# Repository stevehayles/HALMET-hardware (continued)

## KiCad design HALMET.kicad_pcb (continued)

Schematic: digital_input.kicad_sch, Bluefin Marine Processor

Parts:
C1101, C1102, C1103, C1112: 3.3nF; C_0402_1005Metric; LCSC C26404
C1104, C1105, C1106, C1107: 220pF; R_0402_1005Metric; LCSC C1530
C1113, C1114, C1115, C1116: 100nF; C_0402_1005Metric; LCSC C1525
D1103, D1104, D1105, D1113: BAT54S; SOT-323_SC-70; LCSC C12741
J1103, J1104, J1105, J1106: Conn_01x02; PhoenixContact_MCV_1,5_2-G-3.81_1x02_P3.81mm_Vertical; LCSC C8396
JP1101, JP1102, JP1103, JP1104, JP1105, JP1106, JP1107, JP1108, JP1109, JP1110, JP1111, JP1112: SolderJumper_2_Open; SolderJumper-2_P1.3mm_Open_TrianglePad_Narrow
R1101, R1102, R1104, R1105: 20k; R_0603_1608Metric; LCSC C4184
R1106, R1107, R1108, R1109: 100k; R_0402_1005Metric; LCSC C25741
U1101, U1102, U1103, U1104: 74LVC1G17; SOT-353_SC-70-5; LCSC C212314

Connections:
+3.3V_1: C1113.1, C1114.1, C1115.1, C1116.1, D1103.2 (K), D1104.2 (K), D1105.2 (K), D1113.2 (K), JP1106.2 (B), JP1107.2 (B), JP1109.2 (B), JP1111.2 (B), U1101.5 (VCC), U1102.5 (VCC), U1103.5 (VCC), U1104.5 (VCC); also elsewhere on the board
/Digital input/DigIn1: U1101.4; also elsewhere on the board
/Digital input/DigIn2: U1102.4; also elsewhere on the board
/Digital input/DigIn3: U1103.4; also elsewhere on the board
/Digital input/DigIn4: U1104.4; also elsewhere on the board
/Digital input/In1: J1103.2, R1101.2
/Digital input/In2: J1104.2, R1102.2
/Digital input/In3: J1105.2, R1104.2
/Digital input/In4: J1106.2, R1105.2
/Digital input/Inp1: C1104.1, D1113.3 (COM), JP1101.1 (A), R1101.1, R1106.2, U1101.2
/Digital input/Inp2: C1105.1, D1103.3 (COM), JP1102.1 (A), R1102.1, R1107.2, U1102.2
/Digital input/Inp3: C1106.1, D1104.3 (COM), JP1103.1 (A), R1104.1, R1108.2, U1103.2
/Digital input/Inp4: C1107.1, D1105.3 (COM), JP1104.1 (A), R1105.1, R1109.2, U1104.2
GND1: C1101.2, C1102.2, C1103.2, C1104.2, C1105.2, C1106.2, C1107.2, C1112.2, C1113.2, C1114.2, C1115.2, C1116.2, D1103.1 (A), D1104.1 (A), D1105.1 (A), D1113.1 (A), J1103.1, J1104.1, J1105.1, J1106.1, JP1105.1 (A), JP1108.1 (A), JP1110.1 (A), JP1112.1 (A), U1101.3 (GND), U1102.3 (GND), U1103.3 (GND), U1104.3 (GND); also elsewhere on the board
unnamed: C1112.1, JP1101.2 (B)
unnamed: C1101.1, JP1102.2 (B)
unnamed: C1102.1, JP1103.2 (B)
unnamed: C1103.1, JP1104.2 (B)
unnamed: JP1105.2 (B), JP1106.1 (A), R1106.1
unnamed: JP1107.1 (A), JP1108.2 (B), R1107.1
unnamed: JP1109.1 (A), JP1110.2 (B), R1108.1
unnamed: JP1111.1 (A), JP1112.2 (B), R1109.1

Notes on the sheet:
RC LP filter with fc = 36 kHz
Clamp input to rails
Input Connectors
Optional pull-up or pull-down for different NO/NC switch configurations.
Solder jumpers enable optional lowpass filters with f_c at 2.3 kHz
Limit input current in clamped operation

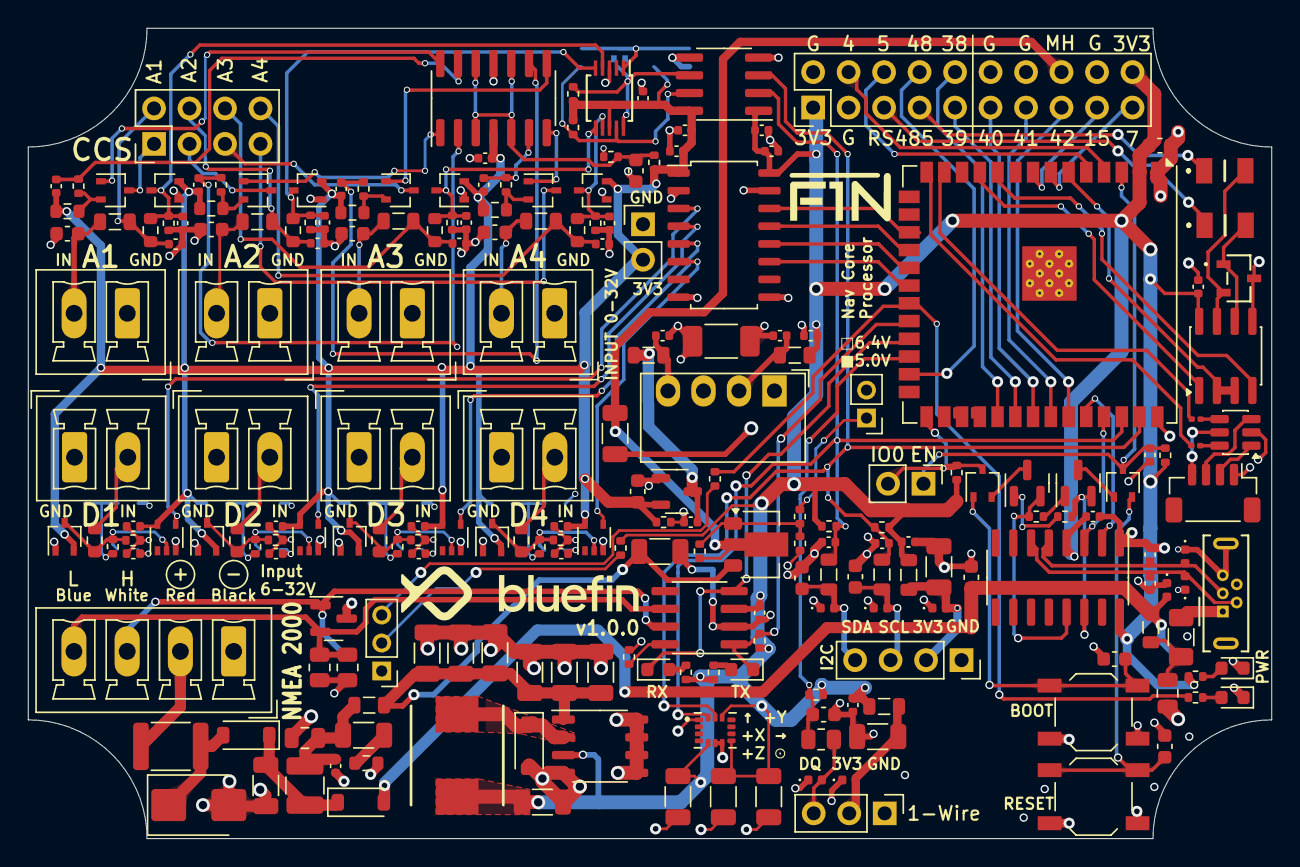
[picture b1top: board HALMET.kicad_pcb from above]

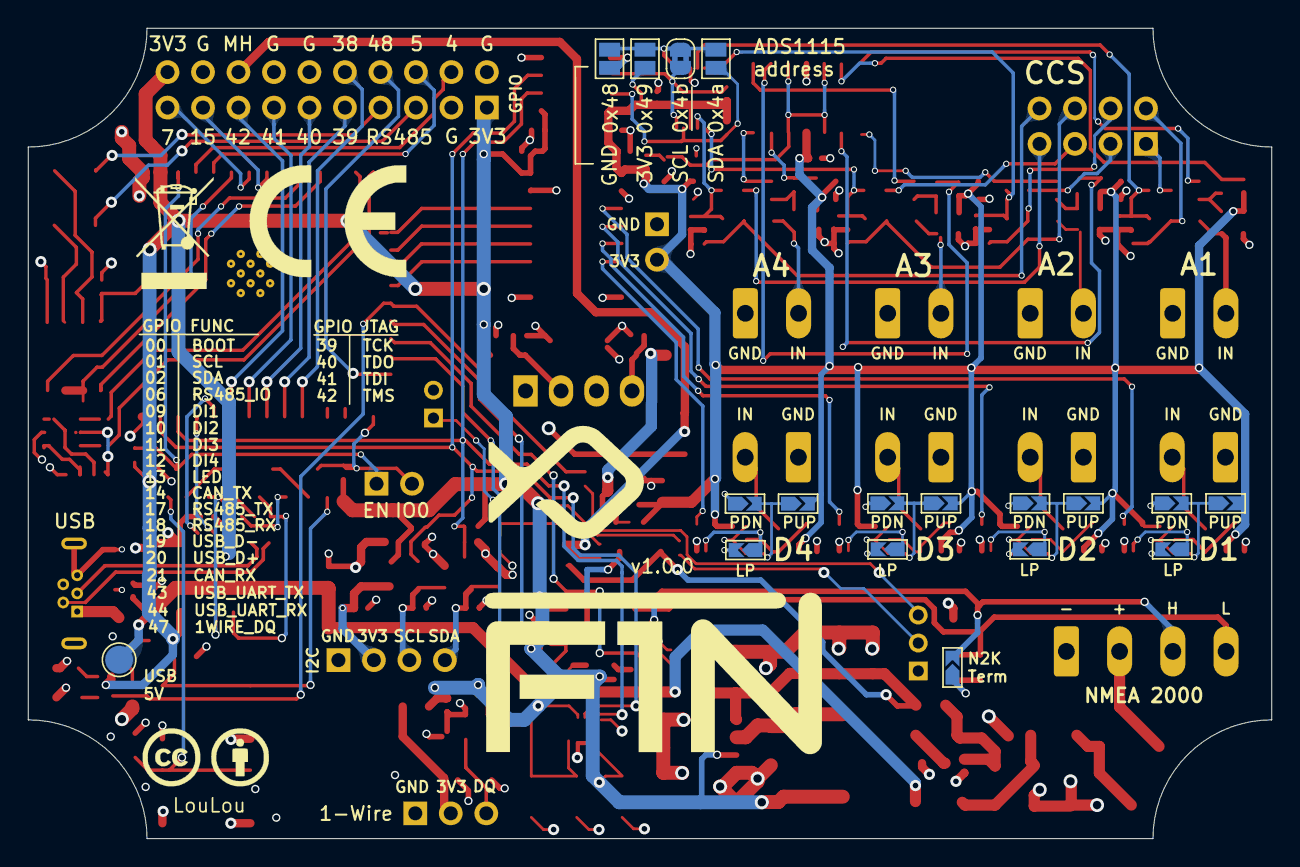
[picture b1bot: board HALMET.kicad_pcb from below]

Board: 4 copper layers, 89.0 x 58.0 mm, 243 parts (20 on the bottom side), 135 nets.

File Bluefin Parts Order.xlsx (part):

Reference | Qty | Value | DNP | Exclude from BOM | Exclude from Board | Footprint | Datasheet | LCSC | JLCPCB_CORRECTION |  |  | New
C1101,C1102,C1103,C1112 | 4 | 3.3nF |  |  |  | Capacitor_SMD:C_0402_1005Metric | ~ | C26404 |  |  |  | 0
C1104,C1105,C1106,C1107 | 4 | 220pF |  |  |  | Resistor_SMD:R_0402_1005Metric | ~ | C1530 |  |  |  | 0
C1201,C1202,C1208,C1210 | 4 | 4.7uF |  |  |  | Capacitor_SMD:C_0402_1005Metric | ~ | C23733 |  |  |  | 0
C1203 | 1 | 10uF/10V |  |  |  | Capacitor_SMD:C_0603_1608Metric | ~ | C19702 |  |  |  | 0
C1209 | 1 | 220pF/2kV |  |  |  | HALMET:C_1808_4520Metric | ~ | C2940747 |  |  |  | 0
C202 | 1 | 22uF |  |  |  | Capacitor_SMD:C_0603_1608Metric | ~ | C59461 |  |  |  | 0
C203 | 1 | 1uF |  |  |  | Capacitor_SMD:C_0402_1005Metric | ~ | C52923 |  |  |  | 0
C304 | 1 | 47uF/6.3V |  |  |  | Capacitor_SMD:C_1206_3216Metric | ~ | C96123 |  |  |  | 0
C402 | 1 | 4.7uF/16V |  |  |  | Capacitor_SMD:C_0603_1608Metric | ~ | C19666 |  |  |  | 0
C403,C404 | 2 | 10pF/50V |  | Excluded from BOM |  | Capacitor_SMD:C_0402_1005Metric | ~ | C32949 |  |  |  | 0
C501,C502 | 2 | 100nF/50V |  |  |  | Capacitor_SMD:C_0603_1608Metric | ~ | C14663 |  |  |  | 0
C503,C715 | 2 | 1uF/50V |  |  |  | Capacitor_SMD:C_0805_2012Metric | ~ | C28323 |  |  |  | 0
C601,C604,C612,C614,C705,C706 | 6 | 33pF/50V |  |  |  | Capacitor_SMD:C_0603_1608Metric | ~ | C1663 |  |  |  | 0
C602,C606,C607,C608,C609,C610,C616,C624,C901,C1113,C1114,C1115,C1116,C1204,C120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 | 17 | 100nF |  |  |  | Capacitor_SMD:C_0402_1005Metric | ~ | C1525 |  |  |  | 1
C603,C605,C613,C615,C702,C703 | 6 | 33pF |  |  |  | Capacitor_SMD:C_0402_1005Metric | ~ | C1562 |  |  |  | 0
C611 | 1 | 68nF |  |  |  | Capacitor_SMD:C_0603_1608Metric | ~ | C31658 |  |  |  | 0
C620,C621,C622,C623 | 4 | 10nF |  |  |  | Capacitor_SMD:C_0402_1005Metric | ~ | C15195 |  |  |  | 0
C701,C801 | 2 | 10uF |  |  |  | Capacitor_SMD:C_0402_1005Metric | ~ | C15525 |  |  |  | 0
C704,C707,C708,C709,C710,C711,C712,C714,C721,C803 | 10 | 10uF/50V |  |  |  | Capacitor_SMD:C_1206_3216Metric | ~ | C13585 |  |  |  | 1
C713 | 1 | 4.7nF/50V |  |  |  | Capacitor_SMD:C_0402_1005Metric | ~ | C1538 |  |  |  | 0
C716 | 1 | 4.7uF/50V |  |  |  | Capacitor_SMD:C_1206_3216Metric | ~ | C29823 |  |  |  | 0
C717,C720 | 2 | 0.1uF/50V |  |  |  | Capacitor_SMD:C_1206_3216Metric | ~ | C24497 |  |  |  | 1
C718 | 1 | 2.2uF/50V |  |  |  | Capacitor_SMD:C_1206_3216Metric | ~ | C50254 |  |  |  | 1
C719 | 1 | 10nF/50V |  |  |  | Capacitor_SMD:C_1206_3216Metric | ~ | C153292 |  |  |  | 1
C802 | 1 | 1nF/50V |  |  |  | Capacitor_SMD:C_0603_1608Metric | ~ | C1588 |  |  |  | 0
CR501 | 1 | PSM712-LF-T7 |  |  |  | PSM712-LF-T7:CR_SOT-23_PTD | PSM712-LF-T7 | C32677 |  |  |  | 1
D1001,D1002 | 2 | GREEN LED |  |  |  | LED_SMD:LED_0603_1608Metric | ~ | C965804 |  |  |  | 0
D1101,D1102 | 2 | BAT54A |  |  |  | Package_TO_SOT_SMD:SOT-323_SC-70 |  | C78261 | 0;0;180 |  |  | 0
D201,D303,D701 | 3 | B5819W |  |  |  | Diode_SMD:D_SOD-123 | ~ | C8598 |  |  |  | 0
D301 | 1 | SMBJ33CA |  |  |  | Diode_SMD:D_SMB | ~ | C114000 |  |  |  | 0
D401,D402,D403,D503,D504,D903,D904,D905 | 8 | ESD5451N |  |  |  | Diode_SMD:D_0402_1005Metric | ~ | C2936977 |  |  |  | 0
D501 | 1 | BLUE LED |  |  |  | LED_SMD:LED_0603_1608Metric | ~ | C84266 |  |  |  | 0
D502 | 1 | RED LED |  |  |  | LED_SMD:LED_0603_1608Metric | ~ | C2286 |  |  |  | 0
D603,D604,D605,D611,D1103,D1104,D1105,D1113 | 8 | BAT54S |  |  |  | Package_TO_SOT_SMD:SOT-323_SC-70 | https://www.diodes.com/assets/Datasheets/ds11005.pdf | C12741 | 0;0;180 |  |  | 0
D801 | 1 | SM24CANB |  |  |  | Package_TO_SOT_SMD:SOT-23 | ~ | C41376477 | 0;0;180 |  |  | 0
F301 | 1 | mSMD050-60V |  |  |  | Fuse:Fuse_1812_4532Metric | ~ | C70113 |  |  |  | 0
F401 | 1 | BSMD1206-100-6V |  |  |  | Fuse:Fuse_1206_3216Metric | https://datasheet.lcsc.com/lcsc/2305121423_BHFUSE-BSMD1206-1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 | C883129 |  |  |  | 0
F501,F502 | 2 | 1206L010/60WR |  |  |  | 1206L010_60WR:1206L075132WR | ~ | C2153714 |  |  |  | 1
FB401,FB701,FB704,FB801 | 4 | GZ2012D601TF |  |  |  | Inductor_SMD:L_0805_2012Metric | ~ | C1017 |  |  |  | 0
FB601,FB602,FB603,FB604,FB702,FB703 | 6 | GZ2012D101TF |  |  |  | Inductor_SMD:L_0805_2012Metric | ~ | C1015 |  |  |  | 0
G601 | 1 | CC-BY |  | Excluded from BOM |  | HALMET:cc-by_5mm | ~ |  |  |  |  | 0
G602 | 1 | CE-logo |  | Excluded from BOM |  | Symbol:CE-Logo_11.2x8mm_SilkScreen | ~ |  |  |  |  | 0
G603 | 1 | WEEE-logo |  | Excluded from BOM | Excluded from board | Symbol:WEEE-Logo_5.6x8mm_SilkScreen | ~ |  |  |  |  | 0
G604 | 1 | OSHW-logo |  | Excluded from BOM | Excluded from board | Symbol:OSHW-Logo2_9.8x8mm_SilkScreen | ~ |  |  |  |  | 0
H1001,H1002 | 2 | MountingHole |  |  |  | HALMET:MountingSlot_3.2mm_M3_Unplated | ~ |  |  |  |  | 0
J201 | 1 | GPIO |  |  |  | Connector_PinHeader_2.54mm:PinHeader_2x10_P2.54mm_Vertical | ~ | C492427 | 1.27;24.13;90 |  |  | 0
J203 | 1 | Conn_01x01 |  | Excluded from BOM |  | TestPoint:TestPoint_Pad_D2.0mm | ~ |  |  |  |  | 0
J302,J1201 | 2 | Conn_01x02 |  |  |  | Connector_PinHeader_2.54mm:PinHeader_1x02_P2.54mm_Vertical | ~ |  |  |  |  | 0
J401 | 1 | USB_B_Micro |  |  |  | Connector_USB:USB_Micro-B_Wuerth_614105150721_Vertical | ~ | C145795 | 1.3;0.5;0 |  |  | 0
J402 | 1 | Conn_01x04 |  |  |  | Connector_JST:JST_SH_BM04B-SRSS-TB_1x04-1MP_P1.00mm_Vertical | ~ | C160390 |  |  |  | 1
J501 | 1 | EXT LEDS |  |  |  | Connector_PinHeader_2.00mm:PinHeader_1x03_P2.00mm_Vertical | ~ | C541857 |  |  |  | 1
J602 | 1 | Conn_02x04_Odd_Even |  |  |  | Connector_PinHeader_2.54mm:PinHeader_2x04_P2.54mm_Vertical | ~ | C124386 | 1.27;3.81;90 |  |  | 0
J604,J605,J606,J607,J1103,J1104,J1105,J1106 | 8 | Conn_01x02 |  |  |  | Connector_Phoenix_MC:PhoenixContact_MCV_1,5_2-G-3.81_1x02_P3.81mm_Vertical | ~ | C8396 | 1.905;0;180 |  |  | 0
J702 | 1 | Conn_01x04 |  |  |  | Connector_PinSocket_2.54mm:PinSocket_1x04_P2.54mm_Vertical | ~ | C124413 | 0;3.81;90 |  |  | 0
J801 | 1 | Conn_01x03 |  |  |  | Connector_PinHeader_2.54mm:PinHeader_1x03_P2.54mm_Vertical | ~ | C49257 | 0;2.54;90 |  |  | 0
J802 | 1 | Conn_01x04 |  |  |  | Connector_Phoenix_MC:PhoenixContact_MCV_1,5_4-G-3.81_1x04_P3.81mm_Vertical | ~ | C8410 | 5.715;0;180 |  |  | 0
JP1 | 1 | Jumper_2_Small_Open |  |  |  | Connector_PinHeader_2.00mm:PinHeader_1x02_P2.00mm_Vertical | ~ | C541856 |  |  |  | 1
JP601,JP1101,JP1102,JP1103,JP1104,JP1105,JP1106,JP1107,JP1108,JP1109,JP1110,JP1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 | 13 | SolderJumper_2_Open |  |  |  | HALMET:SolderJumper-2_P1.3mm_Open_TrianglePad_Narrow | ~ |  |  |  |  | 0
JP602,JP604,JP605 | 3 | Open |  |  |  | Jumper:SolderJumper-2_P1.3mm_Open_Pad1.0x1.5mm | ~ |  |  |  |  | 0
JP603 | 1 | Bridged |  |  |  | Jumper:SolderJumper-2_P1.3mm_Bridged2Bar_RoundedPad1.0x1.5mm | ~ |  |  |  |  | 0
L1201,L1202 | 2 | CMH201209B4R7MT |  |  |  | Inductor_SMD:L_0805_2012Metric | ~ | C394959 |  |  |  | 0
L301 | 1 | SMMS0650-470M |  |  |  | HALMET:SMMS0650-1R0M | ~ | C149588 |  |  |  | 0
L701 | 1 | NLCV32T-100K-EFR |  |  |  | Inductor_SMD:L_1210_3225Metric | ~ | C295195 |  |  |  | 0
PS1201 | 1 | B0305S-1WR3 |  |  |  | Converter_DCDC:Converter_DCDC_Murata_MEE1SxxxxSC_THT |  | C7465186 | 0;3.81;270 |  |  | 0
Q401,Q402 | 2 | S8050 |  |  |  | Package_TO_SOT_SMD:SOT-23 | http://www.unisonic.com.tw/datasheet/S8050.pdf | C2146 | 0;0;180 |  |  | 0
Q601,Q602,Q603,Q604 | 4 | BC856BW,115 |  |  |  | Package_TO_SOT_SMD:SOT-323_SC-70 | ~ | C28063 | 0;0;180 |  |  | 0
R1001,R1002 | 2 | 1.5k |  |  |  | Resistor_SMD:R_0402_1005Metric | ~ | C25867 |  |  |  | 0
R1106,R1107,R1108,R1109 | 4 | 100k |  |  |  | Resistor_SMD:R_0402_1005Metric | ~ | C25741 |  |  |  | 0
R1201 | 1 | 330R |  |  |  | Resistor_SMD:R_0402_1005Metric | ~ | C25104 |  |  |  | 0
R201,R213,R401,R402,R503,R612,R1103 | 7 | 10k |  |  |  | Resistor_SMD:R_0402_1005Metric | ~ | C25744 |  |  |  | 0
R204,R505 | 2 | 240R |  |  |  | Resistor_SMD:R_0402_1005Metric | ~ | C25094 |  |  |  | 1
R205,R603,R604,R605,R606,R611 | 6 | 1k |  |  |  | Resistor_SMD:R_0402_1005Metric | ~ | C11702 |  |  |  | 1
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
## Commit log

2025-12-01 Initial V1.0.0 Bluefin forked
    Added ICM-42688-P 6-axis IMU
    Added LM317 LDO for 6.4v or 5v MHU supply (selectable via jumper)
    Added External LED's for IO2 (Pin 24) and 3.3v
2025-12-01 Increases trace width on the front copper layer
    Increases trace width for better signal integrity or manufacturability on the front copper layer of the PCB.
2025-12-06 Added RS485/RS233 (NMEA 01830) chip
    Added SP3485EN RS485 bi-directional driver with a GPIO toggle for changing input - output direction.
    Connected to GPIO pin header
2025-12-07 Changed to ESP32-S3-WROOM-1U
    Added ESP32-S3-WROOM-1U-N16R2 and updated all routing and pin assignments.
    Added USB-OTG connected via JST-PH
2025-12-07 Added TSV/ESD to the native USB
2025-12-07 Renames IO2 to IO13 for onboard LED
    The original label "IO2" was incorrect and has been updated to "IO13"
    to reflect the intended signal.
2025-12-07 Silkscreen updates
    Back silkscreen bough up-to-date with GPIO pin changes
2025-12-08 Net renaming and Silkscreen tidy ups
    The UART / Serial naming convention is revised for more consistency
2025-12-08 Small track cleanup
2025-12-08 Added ESP32 Pin allocation summary sheet
2025-12-08 Adjust external LED resistor values for ~5 mA drive current
    Added series resistors for optional external panel LEDs on the GPIO13 (blue)
    and 3V3 (red) indicator lines. On-board LEDs retain their existing 2 kΩ
    resistors; external LEDs now use separate resistors sized for ~5 mA.
    Red LED:
    - Vf ≈ 2.1 V
    - Vr = 3.3 V – 2.1 V = 1.2 V
2025-12-08 Changed MCU to ESP32-S3-WROOM-1U-N16R8
    ESP32-S3-WROOM-1U-N16R8 has 8 MB of Octal PSRAM
2025-12-08 Updated LCSC part numbers
2025-12-18 Ignores KiCad lock files.
    Prevents accidental inclusion of KiCad lock files in the repository.
    These files are automatically created by KiCad when a schematic or PCB is open
    and should not be tracked by version control.
2025-12-18 Stop tracking KiCad lock files
2026-01-08 Moved ESP32-S3 + larger pin headers
2026-01-08 Updates LCSC part numbers.
    Updates LCSC part numbers in the schematics and PCB to reflect the correct components.
    This ensures accurate component sourcing and BOM generation.
2026-01-08 Small text cleanups
    Some text too small, minimum now 0.8mm
2026-01-09 Repo tidy up
